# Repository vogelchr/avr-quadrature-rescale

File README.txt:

I had an older piece of hardware which used a quadrature encoder,
unfortunately I wasn't able to purchase the exact replacement, because
I needed a low number of detents *and* only one pulse-step per detent.

The old encoder had detents and quadrature outputs which look like this:

** Old Encoder **

    detents
     v    v    v    v    v    v    v    v    v    v    v    v    v
   +----:----+         +----:----+         +----:----+         +---:-
   |         |         |         |         |         |         |
---+         +----:----+         +----:----+         +----:----+

        +----:----+         +----:----+         +----:----+         +-
        |         |         |         |         |         |         |
---:----+         +----:----+         +----:----+         +----:----+

The new decoders I found did two steps, or even one cycle per detent.

** New Encoder **

  detents
  V       V       V       V       V       V       V
 +-:-+   +-:-+   +-:-+   +-:-+   +-:-+   +-:-+   +-:-+   
 |   |   |   |   |   |   |   |   |   |   |   |   |   |   
-+   +-:-+   +-:-+   +-:-+   +-:-+   +-:-+   +-:-+   +-:-

   +-:-+   +-:-+   +-:-+   +-:-+   +-:-+   +-:-+   +-:-+   
   |   |   |   |   |   |   |   |   |   |   |   |   |   |   
-:-+   +-:-+   +-:-+   +-:-+   +-:-+   +-:-+   +-:-+   +-:-

The enclosing PCB houses a ATTiny26 (one of the most useless chips of the)
attiny series, I think, but I had a few spare. It converts puslses of a
"new encoder", divides then by a ratio of 4 steps/step, and outputs pulses
compatible to the old scheme. That's all it does.

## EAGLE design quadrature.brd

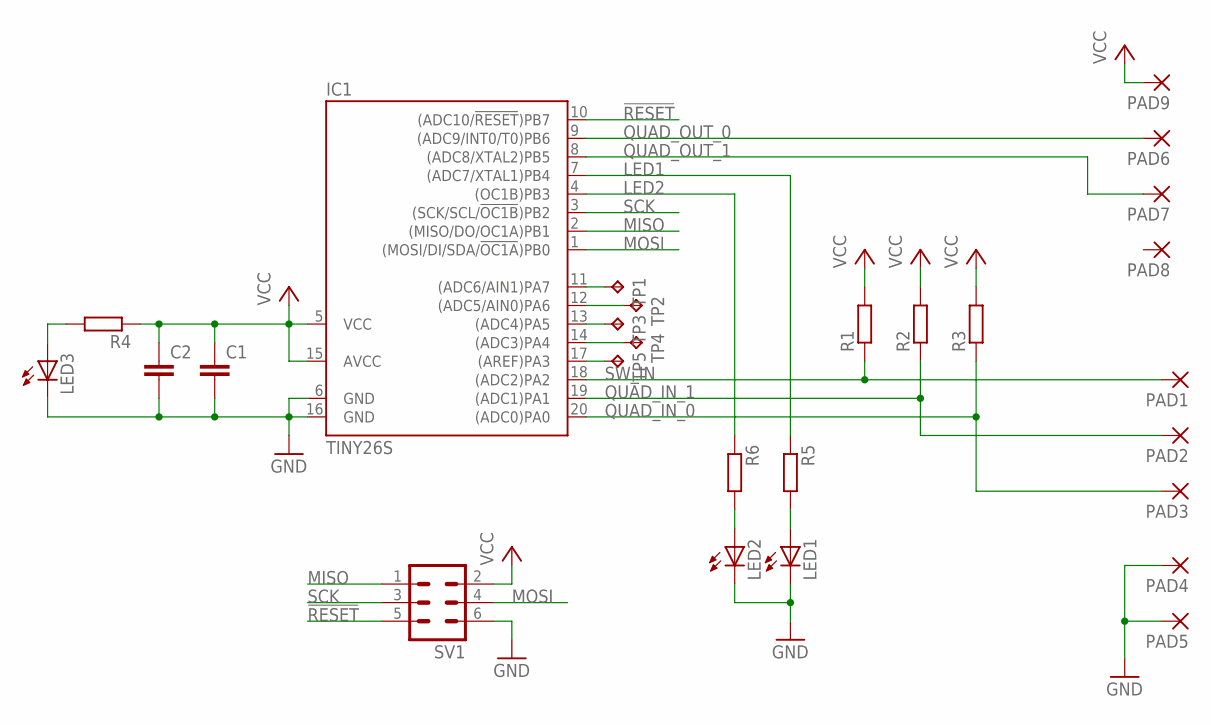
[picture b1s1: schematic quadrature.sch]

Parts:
C1, C2: C-EUC0603; C0603
IC1: TINY26S; SO20L
LED1, LED2, LED3: LEDCHIP-LED0603; CHIP-LED0603
PAD1, PAD2, PAD3, PAD4, PAD5, PAD6, PAD7, PAD8, PAD9: 1,6/0,8
R1, R2, R3, R4, R5, R6: R-EU_R0603; R0603
SV1: ML6
TP1, TP2, TP3, TP4, TP5: TPB1,27; B1,27

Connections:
!RESET: IC1.10 ((ADC10/!RESET!)PB7), SV1.5
GND: C1.2, C2.2, IC1.6 (GND), IC1.16 (GND), LED1.C, LED2.C, LED3.C, PAD4.1, PAD5.1, SV1.6
LED1: IC1.7 ((ADC7/XTAL1)PB4), R5.1
LED2: IC1.4 ((OC1B)PB3), R6.1
MISO: IC1.2 ((MISO/DO/OC1A)PB1), SV1.1
MOSI: IC1.1 ((MOSI/DI/SDA/!OC1A!)PB0), SV1.4
unnamed: IC1.11 ((ADC6/AIN1)PA7), TP1.TP
unnamed: LED3.A, R4.2
unnamed: IC1.12 ((ADC5/AIN0)PA6), TP2.TP
unnamed: IC1.13 ((ADC4)PA5), TP3.TP
unnamed: LED1.A, R5.2
unnamed: LED2.A, R6.2
unnamed: IC1.14 ((ADC3)PA4), TP4.TP
unnamed: IC1.17 ((AREF)PA3), TP5.TP
QUAD_IN_0: IC1.20 ((ADC0)PA0), PAD3.1, R3.1
QUAD_IN_1: IC1.19 ((ADC1)PA1), PAD2.1, R2.1
QUAD_OUT_0: IC1.9 ((ADC9/INT0/T0)PB6), PAD6.1
QUAD_OUT_1: IC1.8 ((ADC8/XTAL2)PB5), PAD7.1
SCK: IC1.3 ((SCK/SCL/!OC1B!)PB2), SV1.3
SW_IN: IC1.18 ((ADC2)PA2), PAD1.1, R1.1
VCC: C1.1, C2.1, IC1.5 (VCC), IC1.15 (AVCC), PAD9.1, R1.2, R2.2, R3.2, R4.1, SV1.2

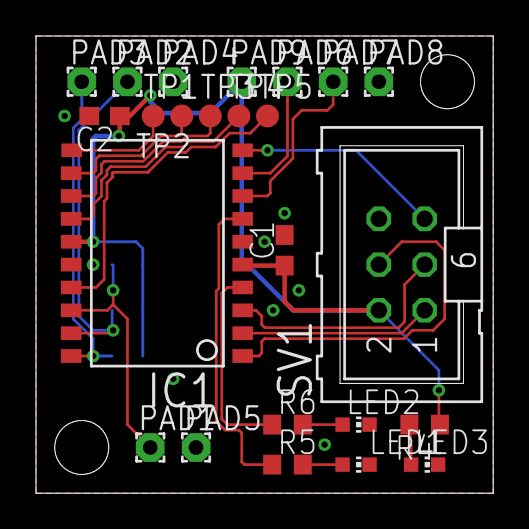
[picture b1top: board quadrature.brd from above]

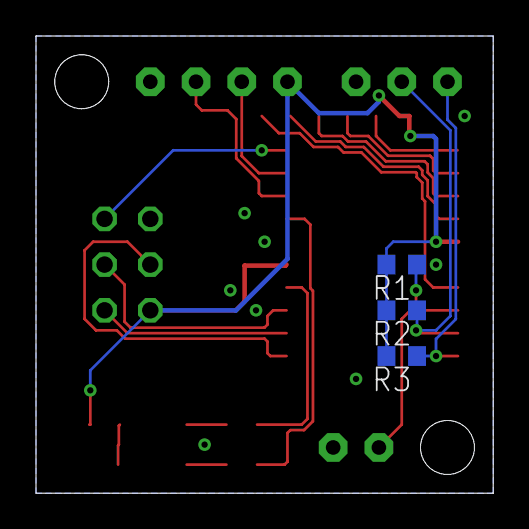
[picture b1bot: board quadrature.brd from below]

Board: 2 copper layers, 25.4 x 25.4 mm, 27 parts (3 on the bottom side), 21 nets.

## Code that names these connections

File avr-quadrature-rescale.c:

#include <avr/io.h>
#include <avr/interrupt.h>
#include <avr/pgmspace.h>

/*
 *
 *               +---------------+
 *  MOSI(ISP)    |  1 PB0 PA0 20 |      QIN0
 *  MISO(ISP)    |  2 PB1 PA1 19 |      QIN1
 *  SCK(ISP)     |  3 PB2 PA2 18 |      Switch
 *  LED2 OC1B    |  4 PB3 PA3 17 |      TP
 *               |  5 Vcc GND 16 |
 *               |  6 GND Vcc 15 |
 *  LED1         |  7 PB4 PA4 14 |      TP
 *  QOUT1        |  8 PB5 PA5 13 |      TP
 *  QOUT0        |  9 PB6 PA6 12 |      TP
 *  \Reset       | 10 PB7 PA7 11 |      TP
 *               +---------------+
 */

/*
 *  Gray encoding of counter cnt:
 *    gray = (bin & 0x03) ^ (0x01 & (bin >> 1))
 *  
 *  Cnt  bin  gray
 *  ---:-----:----
 *   0 : 0 0 : 0 0
 *   1 : 0 1 : 0 1
 *   2 : 1 0 : 1 1
 *   3 : 1 1 : 1 0
 */


const signed char quad_state_tbl[16] PROGMEM = {
	/* index is (old_bin << 2) | new_quadrature */
	[0b0001]=+1, /* from [..] 0 -> [.H] 1 */
	[0b0111]=+1, /* from [.H] 1 -> [HH] 2 */
	[0b1010]=+1, /* from [HH] 2 -> [H.] 3 */
	[0b1100]=+1, /* from [H.] 3 -> [..] 0 */

	[0b0010]=-1, /* from [..] 0 -> [H.] 3 */
	[0b1111]=-1, /* from [H.] 3 -> [HH] 2 */
	[0b1001]=-1, /* from [HH] 2 -> [.H] 1 */
	[0b0100]=-1, /* from [.H] 1 -> [..] 0 */
};

#define DDR_QOUT DDRB
#define PORT_QOUT PORTB
#define BV_QOUT0 _BV(6)
#define BV_QOUT1 _BV(5)

#define PORT_QIN PORTA
#define DDR_QIN  DDRA
#define PIN_QIN  PINA
#define BV_QIN0  _BV(0)
#define BV_QIN1  _BV(1)

#define DDR_LED1  DDRB
#define PORT_LED1 PORTB
#define BV_LED1   _BV(4)

#define DDR_LED2  DDRB
#define PORT_LED2 PORTB
#define BV_LED2   _BV(3)

static void
set_led1(int val) {
	if (val)
		PORT_LED1 |= BV_LED1;
	else
		PORT_LED1 &= ~BV_LED1;
}

static void
set_led2(int val) {
	if (val)
		PORT_LED2 |= BV_LED2;
	else
		PORT_LED2 &= ~BV_LED2;
}

static unsigned char
read_quad_input() {
	unsigned char q = 0;
	/* low active inputs */
	if (!(PIN_QIN & BV_QIN0))
		q |= 0x01;
	if (!(PIN_QIN & BV_QIN1))
		q |= 0x02;
	return q;
}

static void
write_quad_output(unsigned char q) {
	/* low active outputs, pulldown via DDR=1, PORT=0 */
	if (q & 0x01) {
		PORT_QOUT &= ~BV_QOUT0;
		DDR_QOUT  |= BV_QOUT0;
	} else {
		DDR_QOUT &= ~BV_QOUT0;
		PORT_QOUT |= BV_QOUT0;
	}

	if (q & 0x02) {
		PORT_QOUT &= ~BV_QOUT1;
		DDR_QOUT |= BV_QOUT1;
	} else {
		DDR_QOUT &= ~BV_QOUT1;
		PORT_QOUT |= BV_QOUT1;
	}
}

static unsigned char led2_dir;
static uint16_t led2_ctr;

/* timer overflow to amuse the user with a fading led */
ISR(TIMER1_OVF1_vect) {
	unsigned char dir = led2_dir;
	uint16_t ctr = led2_ctr;

#if 0
	if (ctr == 1023)
		dir = 0; /* count down */
	if (ctr == 0)
		dir = 1; /* count up */

	if (dir)
		ctr++;
	else
		ctr--;

	OCR1B = ((ctr >> 2)*(ctr >> 2)) >> 8;
#endif

	led2_ctr = ctr;
	led2_dir = dir;
}

static unsigned char
bin_to_gray(unsigned char ctr)
{
	return (ctr & 0x03) ^ (0x01 & (ctr >> 1));
}

/* static unsigned char quad_last; */
static uint16_t quad_ctr=1; /* don't start at the ffff -> 0000 wraparound! */

static void
process_quadrature() {
	signed char s;
	unsigned char q=0;

	set_led1(quad_ctr & 0x01);
	set_led2(quad_ctr & 0x02);

	q = read_quad_input();
	s = pgm_read_byte(&quad_state_tbl[((quad_ctr & 0x03) << 2) | q]);
	quad_ctr += s;

	/*
	 * The detents are around the 0 mark of the input encoding, hence
	 * we don't want to change the quadrature output when changing
	 * from 0..3, because that would be right on the edge of the detent.
	 * If we output (ctr+1)>>2, that's more towards the middle between
	 * detents.
	 *
	 *  detent
	 *   |                       |                       |
	 *   V                       V                       V
	 *  
	 *   0 --- 1 --- 2 --- 3 --- 4 --- 5 --- 6 --- 7 --- 8 ctr from quad input
	 *   0 --- 0 --- 0 --- 0 --- 1 --- 1 --- 1 --- 1 --- 2 
	 *                        ^                       ^   <--- ctr >> 2
	 *
	 *   1 --- 2 --- 3 --- 4 --- 5 --- 6 --- 7 --- 8 --- 9 ctr + 1
	 *   0 --- 0 --- 0 --- 1 --- 1 --- 1 --- 1 --- 2 --- 2
	 *                  ^                       ^         <--- ctr+1 >> 2
	 *
	 */
	q = bin_to_gray((quad_ctr+1) >> 2);
	write_quad_output(q);

}

int
main() {
	/* setup LEDs */
	DDR_LED1 |= BV_LED1;
	DDR_LED2 |= BV_LED2;
	PORT_LED1 |= BV_LED1;
	PORT_LED2 |= BV_LED2;

	/* inputs, pullup */
	DDR_QIN  &= ~ BV_QIN0; /* QIN0 is input */
	DDR_QIN  &= ~ BV_QIN1; /* QIN0 is input */
	PORT_QIN |= BV_QIN0; /* enable pullup for QIN 0 */
	PORT_QIN |= BV_QIN1; /* enable pullup for QIN 1 */

	/* outputs, enable DDR to pull low */
	DDR_QOUT  &= ~BV_QOUT0;
	DDR_QOUT  &= ~BV_QOUT1;
	PORT_QOUT &= ~BV_QOUT0;
	PORT_QOUT &= ~BV_QOUT1;

#if 0
	/* datasheet pg 73, fast PWM mode, set output on bottom, clr on match */
	TCCR1A = _BV(COM1B1) | _BV(PWM1B);
	TCCR1B = _BV(CS12); /* clkio /256 */
	TIMSK |= _BV(TOIE1) ; /* timer overflow */
	OCR1B = 0x10;
	OCR1C = 0xff;
#endif

	sei(); /* enable interrupts */

	quad_ctr = bin_to_gray(read_quad_input());
	while (1)
		process_quadrature();
}

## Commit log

2018-12-05 Initially empty repository.
2018-12-05 Initial checkin of code.
2018-12-05 eagle pcb files
2018-12-05 .gitignore
2018-12-05 Added a readme.
2018-12-07 Fixed relation from input to gray code, adjust to detent position.
    Adjusted the decoding table, so that it is indexed by counter values
    instead of "old_quadrature_input". We can get rid of one varibale
    that way, also we have a fixed relation from input states to the
    2 MSBs of the counter.
    As the counters are now directly related to the quadrature inputs,
    we can further adjust the point at which the output signals change
2018-12-07 Fix wording in README. Indent -> Detent.
